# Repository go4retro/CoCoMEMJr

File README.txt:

TANDY Color Computer 1 and 2/Dragon 2MB RAM Expansion System

Copyright (C) 2017-18  Jim Brain, RETRO Innovations

These files are free designs; you can redistribute them and/or modify
them under the terms of the Creative Commons Attribution-ShareAlike 
4.0 International License.

You should have received a copy of the license along with this
work. If not, see <http://creativecommons.org/licenses/by-sa/4.0/>.

These files are distributed in the hope that they will be useful,
but WITHOUT ANY WARRANTY; without even the implied warranty of
MERCHANTABILITY or FITNESS FOR A PARTICULAR PURPOSE.  See the
license for more details.

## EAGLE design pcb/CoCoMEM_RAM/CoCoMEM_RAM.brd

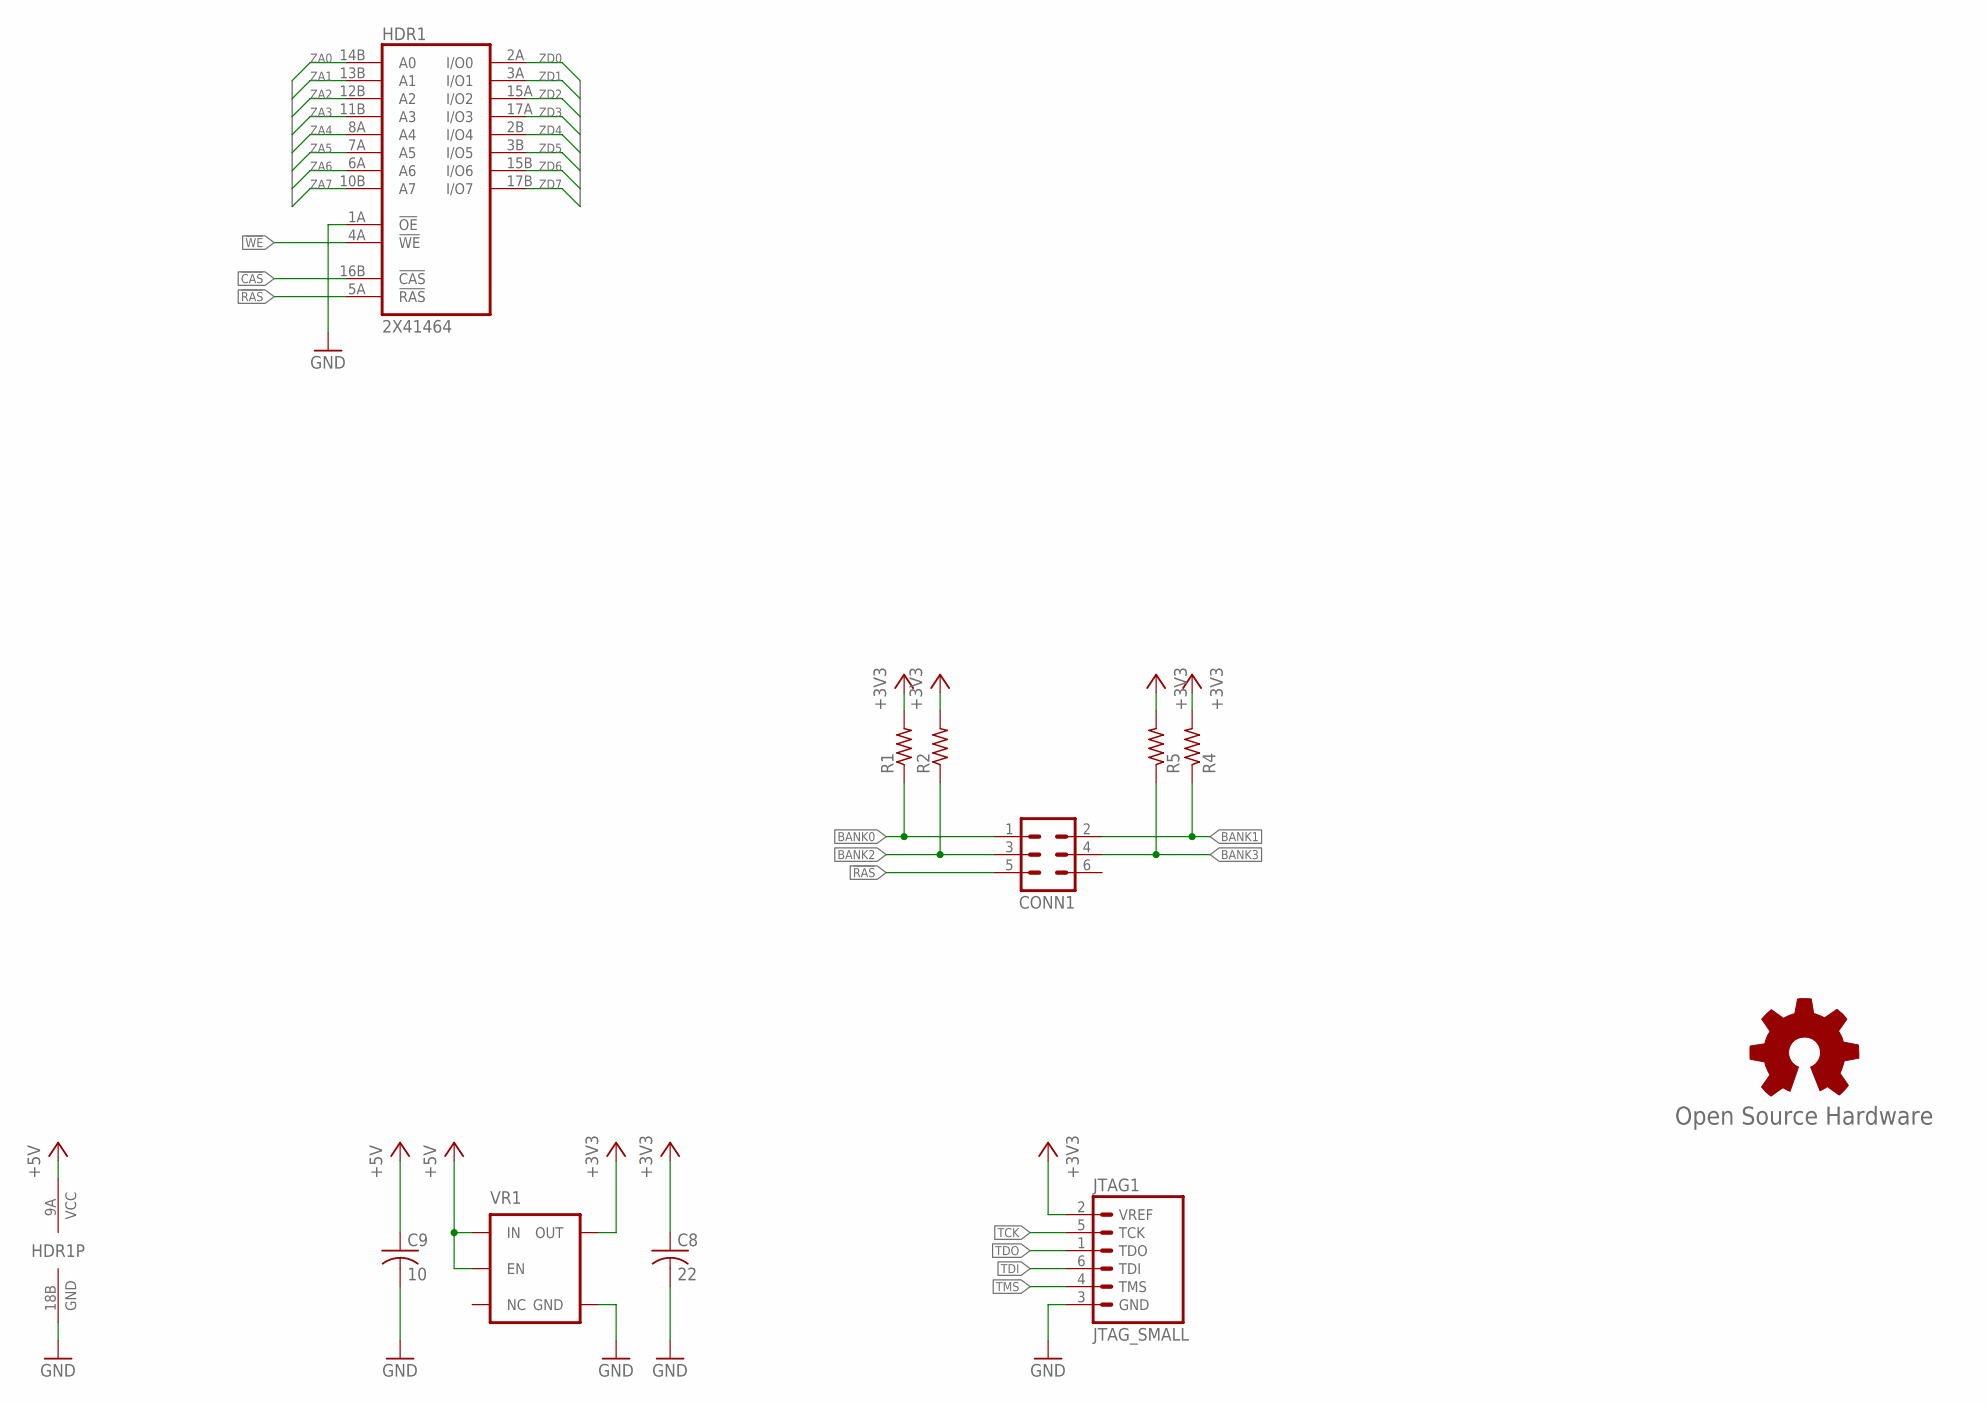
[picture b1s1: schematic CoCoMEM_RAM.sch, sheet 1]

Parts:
C8: 22; C0805
C9: 10; C0805
CONN1: MA03-2
GOLD_ORB_SM1: Open Source Hardware; OSHW_5MM
HDR1: 2X41464; 2XDIL18_REV
JTAG1: JTAG_SMALL; JTAG-6
R1, R2, R4, R5: R-US_R0402; R0402
VR1: V_REG_TPS76433SOT23-5; SOT23-5

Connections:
!CAS: HDR1.16B (!CAS); also elsewhere on the board
!RAS: CONN1.5, HDR1.5A (!RAS); also elsewhere on the board
!WE: HDR1.4A (!WE); also elsewhere on the board
+3V3: C8.1, JTAG1.2 (VREF), R1.2, R2.2, R4.2, R5.2, VR1.5 (OUT); also elsewhere on the board
+5V: C9.1, HDR1.9A (VCC), VR1.1 (IN), VR1.3 (EN)
BANK0: CONN1.1, R1.1; also elsewhere on the board
BANK1: CONN1.2, R4.1; also elsewhere on the board
BANK2: CONN1.3, R2.1; also elsewhere on the board
BANK3: CONN1.4, R5.1; also elsewhere on the board
GND: C8.2, C9.2, HDR1.1A (!OE), HDR1.18B (GND), JTAG1.3 (GND), VR1.2 (GND); also elsewhere on the board
TCK: JTAG1.5 (TCK); also elsewhere on the board
TDI: JTAG1.6 (TDI); also elsewhere on the board
TDO: JTAG1.1 (TDO); also elsewhere on the board
TMS: JTAG1.4 (TMS); also elsewhere on the board
ZA0: HDR1.14B (A0); also elsewhere on the board
ZA1: HDR1.13B (A1); also elsewhere on the board
ZA2: HDR1.12B (A2); also elsewhere on the board
ZA3: HDR1.11B (A3); also elsewhere on the board
ZA4: HDR1.8A (A4); also elsewhere on the board
ZA5: HDR1.7A (A5); also elsewhere on the board
ZA6: HDR1.6A (A6); also elsewhere on the board
ZA7: HDR1.10B (A7); also elsewhere on the board
ZD0: HDR1.2A (I/O0); also elsewhere on the board
ZD1: HDR1.3A (I/O1); also elsewhere on the board
ZD2: HDR1.15A (I/O2); also elsewhere on the board
ZD3: HDR1.17A (I/O3); also elsewhere on the board
ZD4: HDR1.2B (I/O4); also elsewhere on the board
ZD5: HDR1.3B (I/O5); also elsewhere on the board
ZD6: HDR1.15B (I/O6); also elsewhere on the board
ZD7: HDR1.17B (I/O7); also elsewhere on the board

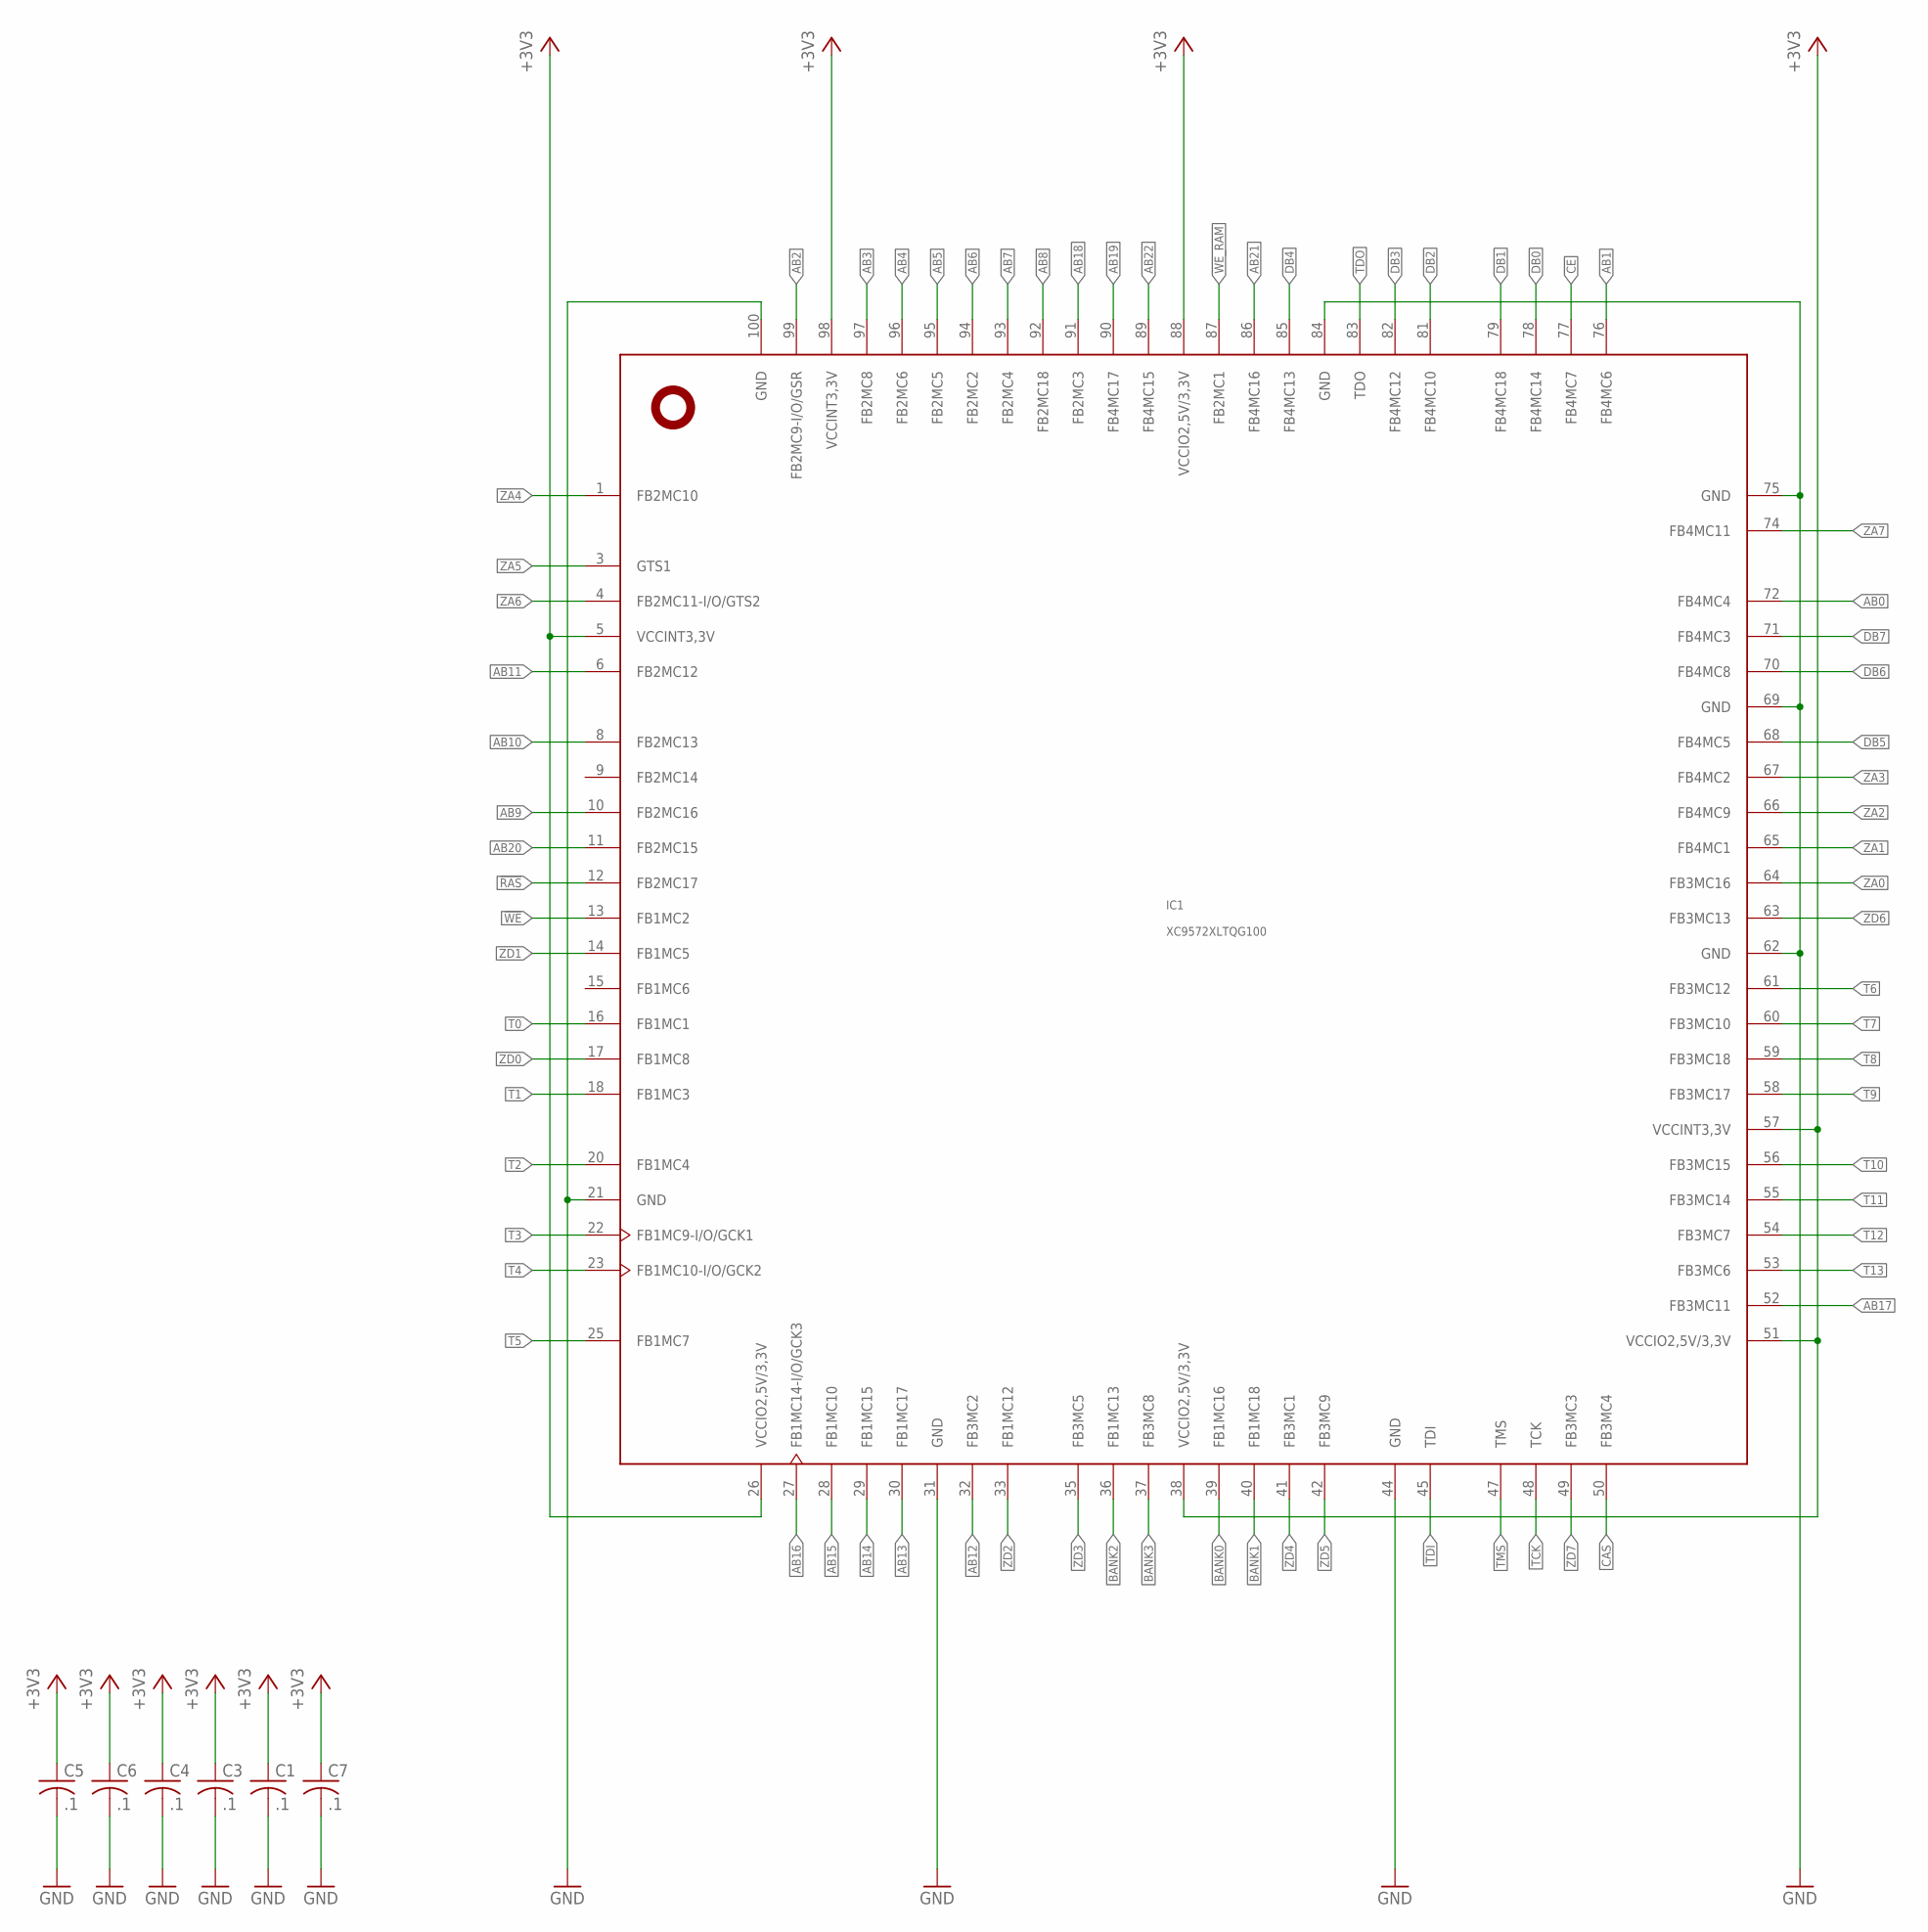
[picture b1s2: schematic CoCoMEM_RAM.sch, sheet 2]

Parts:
C1, C3, C4, C5, C6, C7: .1; C0603
IC1: XC9572XLTQG100; TQFP100

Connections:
!CAS: IC1.50 (FB3MC4); also elsewhere on the board
!CE: IC1.77 (FB4MC7); also elsewhere on the board
!RAS: IC1.12 (FB2MC17); also elsewhere on the board
!WE: IC1.13 (FB1MC2); also elsewhere on the board
!WE_RAM: IC1.87 (FB2MC1); also elsewhere on the board
+3V3: C1.1, C3.1, C4.1, C5.1, C6.1, C7.1, IC1.5 (VCCINT3,3V), IC1.26 (VCCIO2,5V/3,3V), IC1.38 (VCCIO2,5V/3,3V), IC1.51 (VCCIO2,5V/3,3V), IC1.57 (VCCINT3,3V), IC1.88 (VCCIO2,5V/3,3V), IC1.98 (VCCINT3,3V); also elsewhere on the board
AB0: IC1.72 (FB4MC4); also elsewhere on the board
AB1: IC1.76 (FB4MC6); also elsewhere on the board
AB2: IC1.99 (FB2MC9-I/O/GSR); also elsewhere on the board
AB3: IC1.97 (FB2MC8); also elsewhere on the board
AB4: IC1.96 (FB2MC6); also elsewhere on the board
AB5: IC1.95 (FB2MC5); also elsewhere on the board
AB6: IC1.94 (FB2MC2); also elsewhere on the board
AB7: IC1.93 (FB2MC4); also elsewhere on the board
AB8: IC1.92 (FB2MC18); also elsewhere on the board
AB9: IC1.10 (FB2MC16); also elsewhere on the board
AB10: IC1.8 (FB2MC13); also elsewhere on the board
AB11: IC1.6 (FB2MC12); also elsewhere on the board
AB12: IC1.32 (FB3MC2); also elsewhere on the board
AB13: IC1.30 (FB1MC17); also elsewhere on the board
AB14: IC1.29 (FB1MC15); also elsewhere on the board
AB15: IC1.28 (FB1MC10); also elsewhere on the board
AB16: IC1.27 (FB1MC14-I/O/GCK3); also elsewhere on the board
AB17: IC1.52 (FB3MC11); also elsewhere on the board
AB18: IC1.91 (FB2MC3); also elsewhere on the board
AB19: IC1.90 (FB4MC17); also elsewhere on the board
AB20: IC1.11 (FB2MC15); also elsewhere on the board
AB21: IC1.86 (FB4MC16); also elsewhere on the board
AB22: IC1.89 (FB4MC15); also elsewhere on the board
BANK0: IC1.39 (FB1MC16); also elsewhere on the board
BANK1: IC1.40 (FB1MC18); also elsewhere on the board
BANK2: IC1.36 (FB1MC13); also elsewhere on the board
BANK3: IC1.37 (FB3MC8); also elsewhere on the board
DB0: IC1.78 (FB4MC14); also elsewhere on the board
DB1: IC1.79 (FB4MC18); also elsewhere on the board
DB2: IC1.81 (FB4MC10); also elsewhere on the board
DB3: IC1.82 (FB4MC12); also elsewhere on the board
DB4: IC1.85 (FB4MC13); also elsewhere on the board
DB5: IC1.68 (FB4MC5); also elsewhere on the board
DB6: IC1.70 (FB4MC8); also elsewhere on the board
DB7: IC1.71 (FB4MC3); also elsewhere on the board
GND: C1.2, C3.2, C4.2, C5.2, C6.2, C7.2, IC1.21 (GND), IC1.31 (GND), IC1.44 (GND), IC1.62 (GND), IC1.69 (GND), IC1.75 (GND), IC1.84 (GND), IC1.100 (GND); also elsewhere on the board
T0: IC1.16 (FB1MC1)
T1: IC1.18 (FB1MC3)
T2: IC1.20 (FB1MC4)
T3: IC1.22 (FB1MC9-I/O/GCK1)
T4: IC1.23 (FB1MC10-I/O/GCK2)
T5: IC1.25 (FB1MC7)
T6: IC1.61 (FB3MC12)
T7: IC1.60 (FB3MC10)
T8: IC1.59 (FB3MC18)
T9: IC1.58 (FB3MC17)
T10: IC1.56 (FB3MC15)
T11: IC1.55 (FB3MC14)
T12: IC1.54 (FB3MC7)
T13: IC1.53 (FB3MC6)
TCK: IC1.48 (TCK); also elsewhere on the board
TDI: IC1.45 (TDI); also elsewhere on the board
TDO: IC1.83 (TDO); also elsewhere on the board
TMS: IC1.47 (TMS); also elsewhere on the board
ZA0: IC1.64 (FB3MC16); also elsewhere on the board
ZA1: IC1.65 (FB4MC1); also elsewhere on the board
ZA2: IC1.66 (FB4MC9); also elsewhere on the board
ZA3: IC1.67 (FB4MC2); also elsewhere on the board
ZA4: IC1.1 (FB2MC10); also elsewhere on the board
ZA5: IC1.3 (GTS1); also elsewhere on the board
ZA6: IC1.4 (FB2MC11-I/O/GTS2); also elsewhere on the board
ZA7: IC1.74 (FB4MC11); also elsewhere on the board
ZD0: IC1.17 (FB1MC8); also elsewhere on the board
ZD1: IC1.14 (FB1MC5); also elsewhere on the board
ZD2: IC1.33 (FB1MC12); also elsewhere on the board
ZD3: IC1.35 (FB3MC5); also elsewhere on the board
ZD4: IC1.41 (FB3MC1); also elsewhere on the board
ZD5: IC1.42 (FB3MC9); also elsewhere on the board
ZD6: IC1.63 (FB3MC13); also elsewhere on the board
ZD7: IC1.49 (FB3MC3); also elsewhere on the board

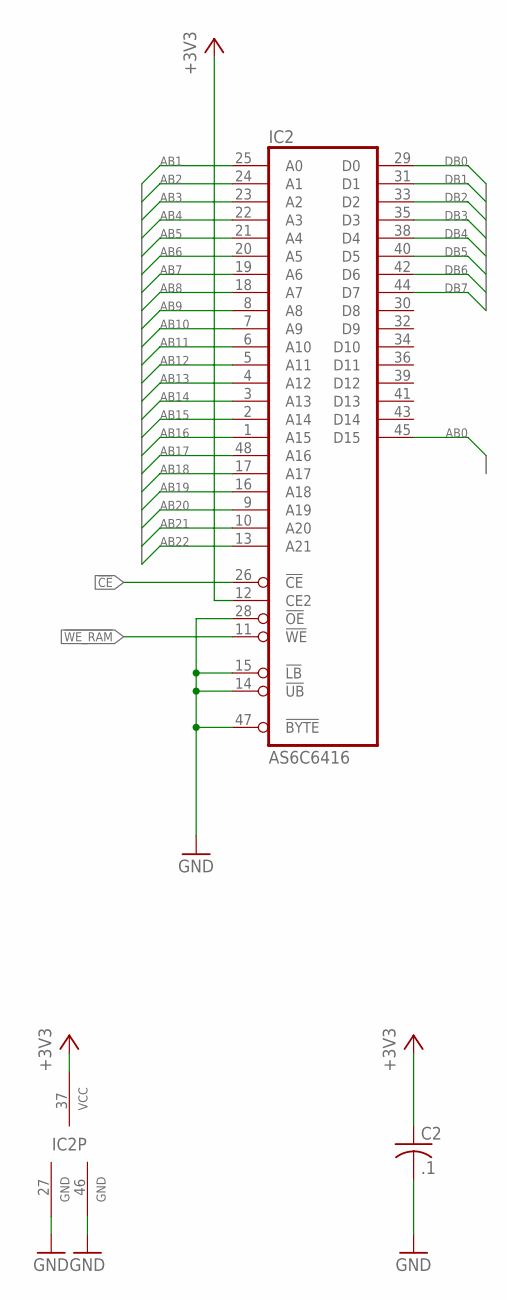
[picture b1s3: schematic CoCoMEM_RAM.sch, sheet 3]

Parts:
C2: .1; C0603
IC2: AS6C6416; TSOP48

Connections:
!CE: IC2.26 (!CE); also elsewhere on the board
!WE_RAM: IC2.11 (!WE); also elsewhere on the board
+3V3: C2.1, IC2.12 (CE2), IC2.37 (VCC); also elsewhere on the board
AB0: IC2.45 (D15); also elsewhere on the board
AB1: IC2.25 (A0); also elsewhere on the board
AB2: IC2.24 (A1); also elsewhere on the board
AB3: IC2.23 (A2); also elsewhere on the board
AB4: IC2.22 (A3); also elsewhere on the board
AB5: IC2.21 (A4); also elsewhere on the board
AB6: IC2.20 (A5); also elsewhere on the board
AB7: IC2.19 (A6); also elsewhere on the board
AB8: IC2.18 (A7); also elsewhere on the board
AB9: IC2.8 (A8); also elsewhere on the board
AB10: IC2.7 (A9); also elsewhere on the board
AB11: IC2.6 (A10); also elsewhere on the board
AB12: IC2.5 (A11); also elsewhere on the board
AB13: IC2.4 (A12); also elsewhere on the board
AB14: IC2.3 (A13); also elsewhere on the board
AB15: IC2.2 (A14); also elsewhere on the board
AB16: IC2.1 (A15); also elsewhere on the board
AB17: IC2.48 (A16); also elsewhere on the board
AB18: IC2.17 (A17); also elsewhere on the board
AB19: IC2.16 (A18); also elsewhere on the board
AB20: IC2.9 (A19); also elsewhere on the board
AB21: IC2.10 (A20); also elsewhere on the board
AB22: IC2.13 (A21); also elsewhere on the board
DB0: IC2.29 (D0); also elsewhere on the board
DB1: IC2.31 (D1); also elsewhere on the board
DB2: IC2.33 (D2); also elsewhere on the board
DB3: IC2.35 (D3); also elsewhere on the board
DB4: IC2.38 (D4); also elsewhere on the board
DB5: IC2.40 (D5); also elsewhere on the board
DB6: IC2.42 (D6); also elsewhere on the board
DB7: IC2.44 (D7); also elsewhere on the board
GND: C2.2, IC2.14 (!UB), IC2.15 (!LB), IC2.27 (GND), IC2.28 (!OE), IC2.46 (GND), IC2.47 (!BYTE); also elsewhere on the board

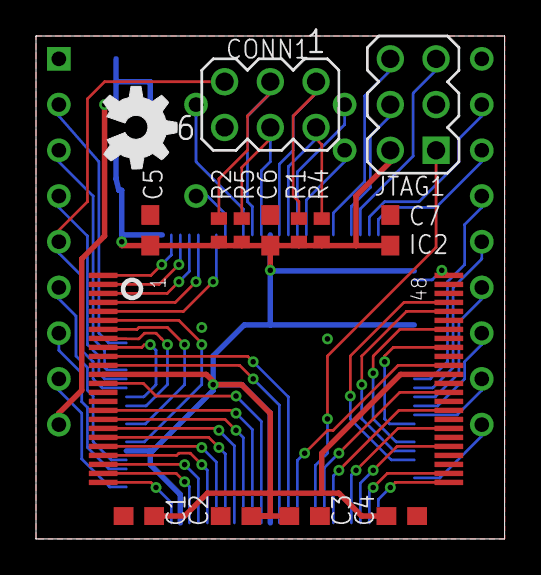
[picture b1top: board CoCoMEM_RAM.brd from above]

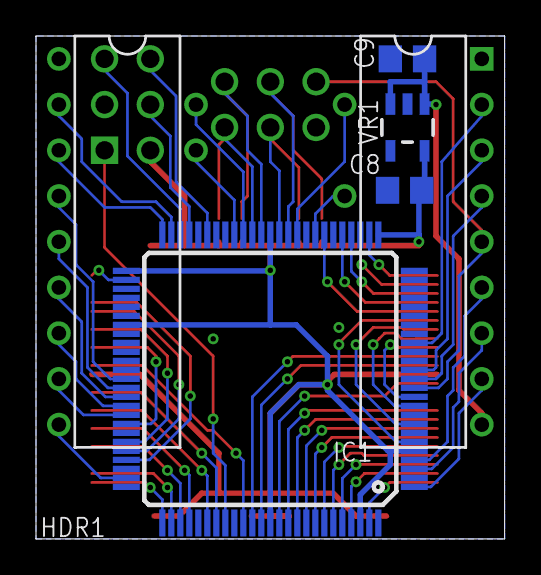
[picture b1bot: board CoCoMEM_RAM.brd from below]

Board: 2 copper layers, 26.0 x 27.9 mm, 20 parts (4 on the bottom side), 63 nets.

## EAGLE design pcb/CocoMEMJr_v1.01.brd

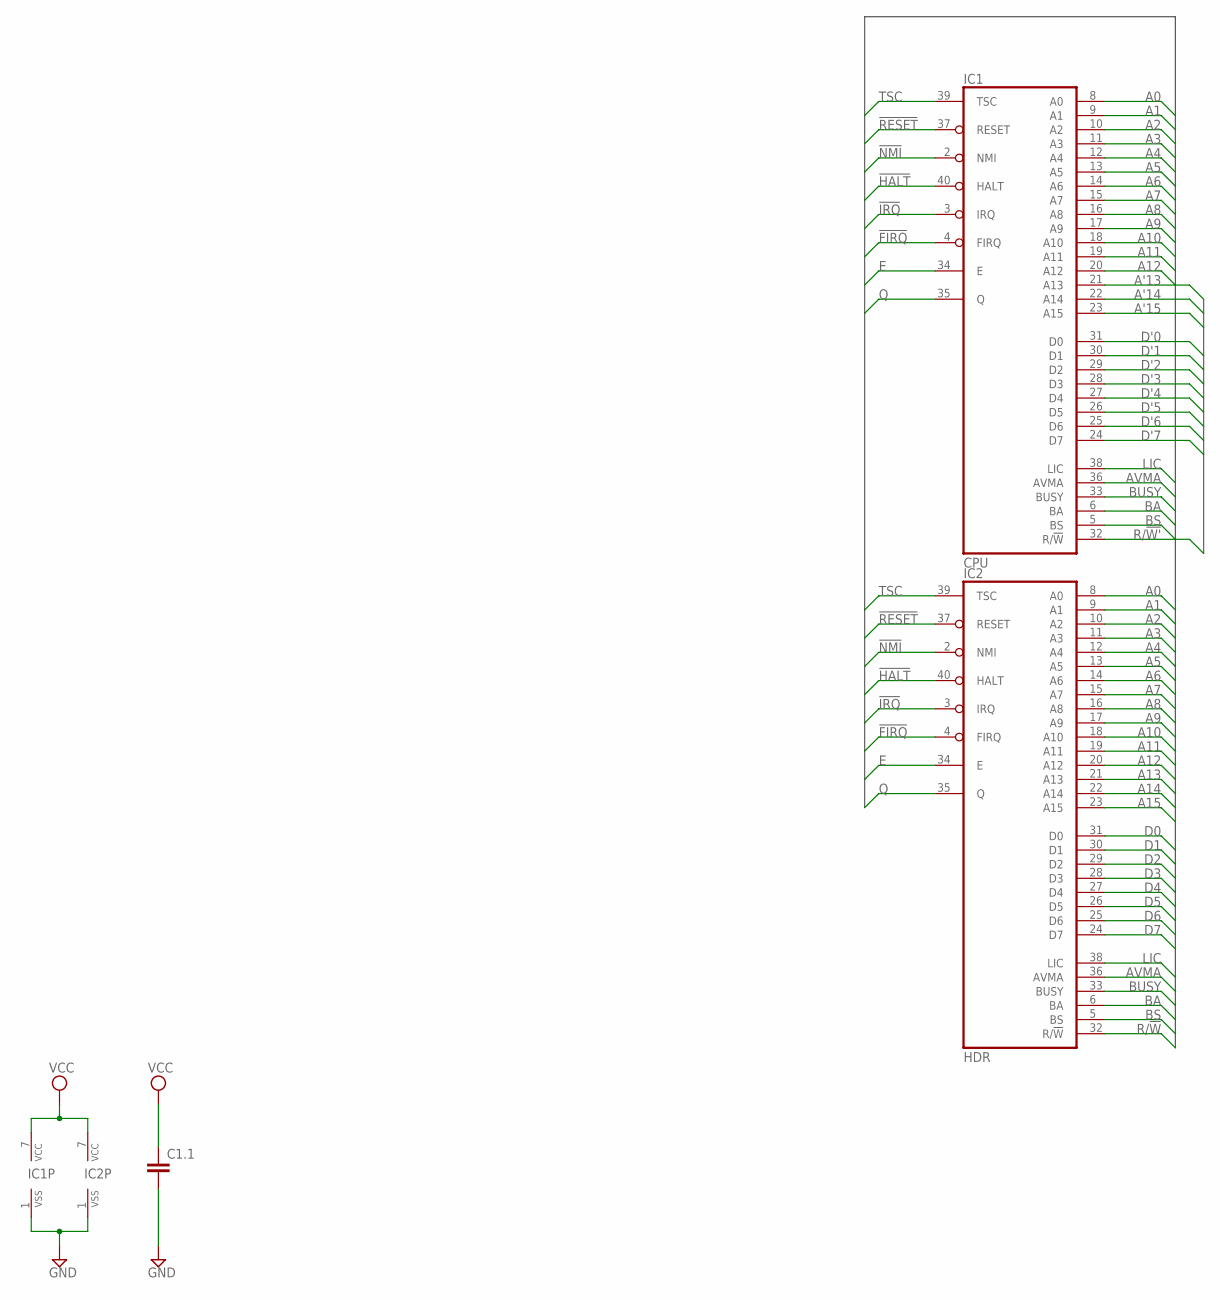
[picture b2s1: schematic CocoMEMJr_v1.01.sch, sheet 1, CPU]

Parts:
C1.1: C-EUC0402; C0402
IC1: CPU; DIL40-ROUNDPAD
IC2: HDR; DIL40-ROUNDPAD

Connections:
!FIRQ: IC1.4 (FIRQ), IC2.4 (FIRQ); also elsewhere on the board
!HALT: IC1.40 (HALT), IC2.40 (HALT); also elsewhere on the board
!IRQ: IC1.3 (IRQ), IC2.3 (IRQ); also elsewhere on the board
!NMI: IC1.2 (NMI), IC2.2 (NMI); also elsewhere on the board
!RESET: IC1.37 (RESET), IC2.37 (RESET); also elsewhere on the board
A0: IC1.8 (A0), IC2.8 (A0); also elsewhere on the board
A1: IC1.9 (A1), IC2.9 (A1); also elsewhere on the board
A2: IC1.10 (A2), IC2.10 (A2); also elsewhere on the board
A3: IC1.11 (A3), IC2.11 (A3); also elsewhere on the board
A4: IC1.12 (A4), IC2.12 (A4); also elsewhere on the board
A5: IC1.13 (A5), IC2.13 (A5); also elsewhere on the board
A6: IC1.14 (A6), IC2.14 (A6); also elsewhere on the board
A7: IC1.15 (A7), IC2.15 (A7); also elsewhere on the board
A8: IC1.16 (A8), IC2.16 (A8); also elsewhere on the board
A9: IC1.17 (A9), IC2.17 (A9); also elsewhere on the board
A10: IC1.18 (A10), IC2.18 (A10); also elsewhere on the board
A11: IC1.19 (A11), IC2.19 (A11); also elsewhere on the board
A12: IC1.20 (A12), IC2.20 (A12); also elsewhere on the board
A13: IC2.21 (A13); also elsewhere on the board
A14: IC2.22 (A14); also elsewhere on the board
A15: IC2.23 (A15); also elsewhere on the board
A'13: IC1.21 (A13); also elsewhere on the board
A'14: IC1.22 (A14); also elsewhere on the board
A'15: IC1.23 (A15); also elsewhere on the board
AVMA: IC1.36 (AVMA), IC2.36 (AVMA)
BA: IC1.6 (BA), IC2.6 (BA); also elsewhere on the board
BS: IC1.5 (BS), IC2.5 (BS); also elsewhere on the board
BUSY: IC1.33 (BUSY), IC2.33 (BUSY); also elsewhere on the board
D0: IC2.31 (D0); also elsewhere on the board
D1: IC2.30 (D1); also elsewhere on the board
D2: IC2.29 (D2); also elsewhere on the board
D3: IC2.28 (D3); also elsewhere on the board
D4: IC2.27 (D4); also elsewhere on the board
D5: IC2.26 (D5); also elsewhere on the board
D6: IC2.25 (D6); also elsewhere on the board
D7: IC2.24 (D7); also elsewhere on the board
D'0: IC1.31 (D0); also elsewhere on the board
D'1: IC1.30 (D1); also elsewhere on the board
D'2: IC1.29 (D2); also elsewhere on the board
D'3: IC1.28 (D3); also elsewhere on the board
D'4: IC1.27 (D4); also elsewhere on the board
D'5: IC1.26 (D5); also elsewhere on the board
D'6: IC1.25 (D6); also elsewhere on the board
D'7: IC1.24 (D7); also elsewhere on the board
E: IC1.34 (E), IC2.34 (E); also elsewhere on the board
GND: C1.1.2, IC1.1 (VSS), IC2.1 (VSS); also elsewhere on the board
LIC: IC1.38 (LIC), IC2.38 (LIC); also elsewhere on the board
Q: IC1.35 (Q), IC2.35 (Q); also elsewhere on the board
R/!W: IC2.32 (R/!W); also elsewhere on the board
R/!W': IC1.32 (R/!W); also elsewhere on the board
TSC: IC1.39 (TSC), IC2.39 (TSC); also elsewhere on the board
VCC: C1.1.1, IC1.7 (VCC), IC2.7 (VCC); also elsewhere on the board

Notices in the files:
parts and their libraries:
SparkFun: Licensing: CC v3.0 Share-Alike You are welcome to use this library for commercial purposes.
